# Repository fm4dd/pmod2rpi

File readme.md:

## PMOD2RPI

### Description

PMOD2RPI is a PMOD-compatible Interface Board for the Raspberry Pi B-type GPIO connector. It provides a total of four PMOD connectors to run PMOD-compatible modules on the Raspberry Pi.  This board is compatible to PMOD interface standard v1.3.1 by Digilent Inc. The PMOD (peripheral module interface) standard enables simple plug-in connectivity between FPGA or microcontroller development boards, and a range of input/output modules.

This design is registered under the OSHWA Open Source Hardware Self-Certification:  

 While all connectors provide digital IO, they also double as serial bus connectors for I2C and SPI modules. To aid troubleshooting, a set of Keystone miniature testpins can be fitted to create access for oscilloscope and DMM monitoring. A Seeeduino XIAO footprint has been added to additionally drive two of the four PMOD's, or to communicate with the RPi. The XIAO is optional, and can operate with the board "standalone" if needed.

#### I2C /SPI signal switching on PMOD1

The PMOD interface standard v1.3.1 added a new extended I2C connector type 6A, which runs the I2C bus signals over the same pins 3/4 that are already used for SPI. In order to allow both bus types to be used on a single connector, switch SW3 allows to swap the I2C signals between pins 3/4 and 9/10 on PMOD1.

See also http://fpga.fm4dd.com/

### Schematic

### Hardware Versions

| Version | Gerber | Schema |
|---------|--------|--------|
| 1.0     |[20210821-pmod2rpi-gerber-v10.zip](release/v10/20210821-pmod2rpi-gerber-v10.zip) | [20210821-pmod2rpi-schema-v10.pdf](release/v10/20210821-pmod2rpi-schema-v10.pdf) |

### Pin Assignments

Pin assigments are listed in the separate [pmod2rpi-pinout.md](pmod2rpi-pinout.md) file.
Below are simplified schematics for the XIAO MCU-specific connectivity.

#### XIAO - PMOD1:

A multi-purpose double-row connector that can used as GPIO Type-1 and Type-1A, SPI Type-2 and Type-2A, or I2C Type-6 or Type-6A, depending on the pin configuration of the XIAO.

#### XIAO - PMOD2:

A double-row connector that can use only the upper row for GPIO Type-1, SPI Type-2, or I2C Type-6 configurations. The lower pins are connected to the Raspberry Pi only.

#### XIAO - Raspberry Pi:

A set of XIAO pins are shared with the Raspberry Pi that can be used to establish GPIO and SPI connections. With bitbanging, I2C is also possible for data exchange between the Pi and the XIAO.

### Example Code

| Platform | Folder | Description |
|----------|--------|-------------|
|Raspberry Pi |[pi-gpiotest](examples/pi-gpiotest)   | simple GPIO test program for digital IO PMODs, such as Digilent's PMOD8LD |
|Raspberry Pi |[pi-tca6424a](https://github.com/fm4dd/pmod-i2c24io/tree/master/examples/pi-tca6424a)   | I2C module driver 'C' program to control the I2C expander module PMOD-I2C24IO connected to PMOD4 |
|Arduino      |[xiao-digital-io](examples/xiao-digital-io)   | Tests digital IO using the Digilent 8-Led PMOD 8LD connected to PMOD1 |
|Arduino      |[xiao-pmod1-24iodemo](https://github.com/fm4dd/pmod-i2c24io/tree/master/examples/xiao-pmod1-24iodemo)   | Creates a lightshow demo by rotating binary patterns over the 24 IO pins, lighting up connected LEDs |

I2C24IO PMOD demos are stored within the PMOD's repo located at [https://github.com/fm4dd/pmod-i2c24io](https://github.com/fm4dd/pmod-i2c24io).

### Board Pictures
I2C24IO PMOD connected to the RPi PMOD Interface board connector PMOD1, running the "xiao-pmod1-i2c24io" example program on the Seeeduino XIAO (Cortex M0) in "standalone" mode:

Raspberry Pi I2C signal measurements on the PMOD2RPI board:

Raspberry Pi operating the I2C24IO-PMOD module connected to PMOD4 on the PMOD2RPI board:

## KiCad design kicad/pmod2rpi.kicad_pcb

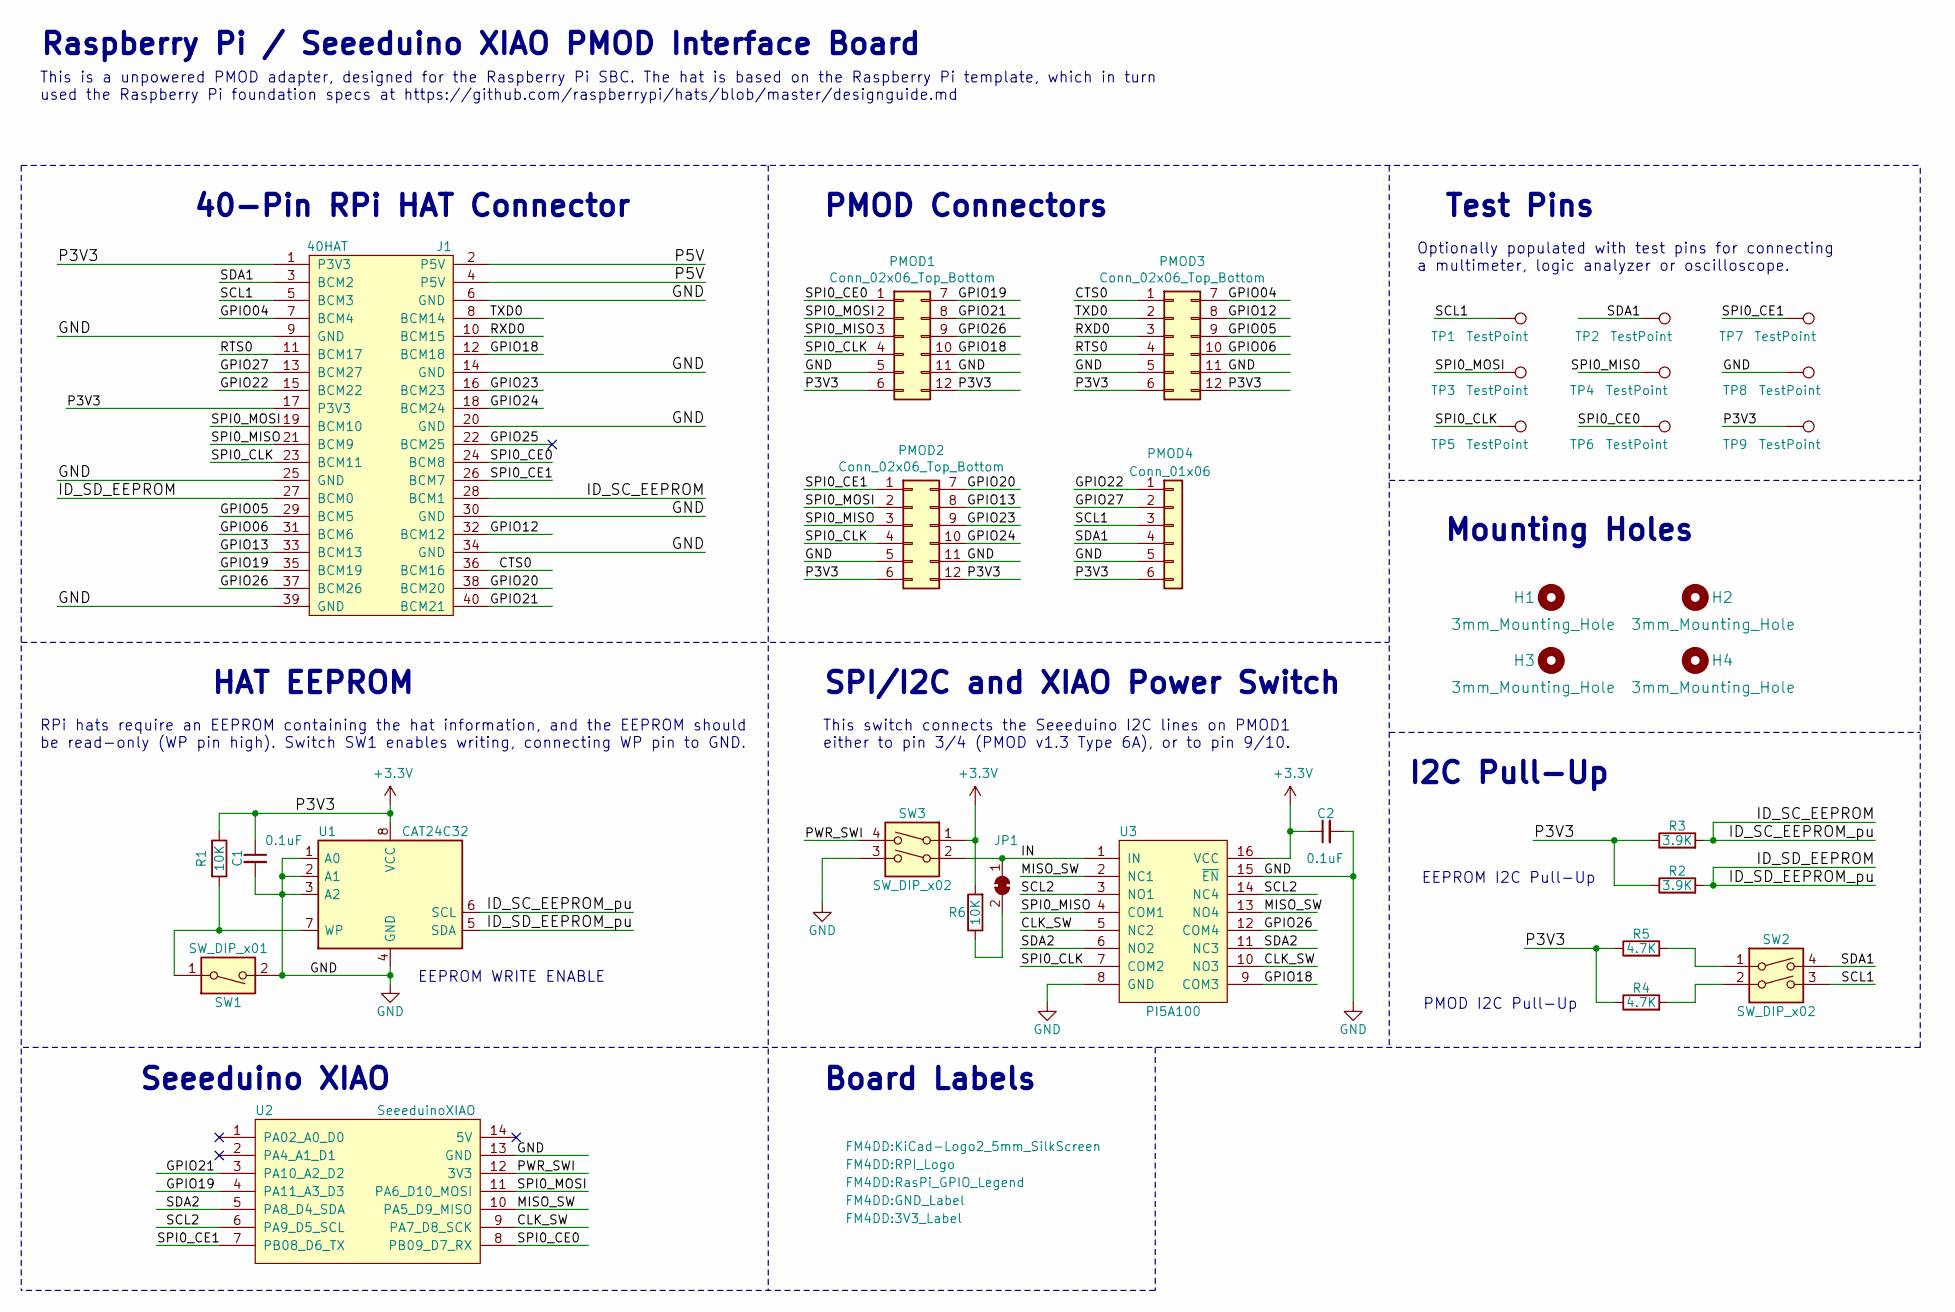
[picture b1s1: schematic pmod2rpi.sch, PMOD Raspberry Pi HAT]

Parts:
C1, C2: 0.1uF; C_0402_1005Metric
H1, H2, H3, H4: 3mm_Mounting_Hole; NPTH_3mm_ID
J1: 40HAT; PinSocket_2x20_P2.54mm_Vertical
JP1: SolderJumper_2_Bridged; SolderJumper-2_P1.3mm_Bridged_Pad1.0x1.5mm
L1: Logo_KiCad_5mm; KiCad-Logo2_5mm_SilkScreen
L2: Logo_RPI; RPI_Logo
L3: Pinout_RPI_GPIO; RasPi_GPIO_Legend
L4: GND_Label
L5: 3V3_Label
PMOD1, PMOD2, PMOD3: Conn_02x06_Top_Bottom; PMODPinSocket_2x06_P2.54mm_Horizontal
PMOD4: Conn_01x06; PMODPinSocket_1x06_P2.54mm_Horizontal
R1, R6: 10K; R_0603_1608Metric
R2, R3: 3.9K; R_0603_1608Metric
R4, R5: 4.7K; R_0603_1608Metric
SW1: SW_DIP_x01; SW_DIP_SPSTx01_XKB_DSIC01LS
SW2, SW3: SW_DIP_x02; SW_DIP_SPSTx02_XKB_DSIC02LS
TP1, TP2, TP3, TP4, TP5, TP6, TP7, TP8, TP9: TestPoint; TestPoint_Keystone_5000-5004_Miniature
U1: CAT24C32; SOIC-8_3.9x4.9mm_P1.27mm
U2: SeeeduinoXIAO; SeeeduinoXIAO-14P-2.54-21X17.8MM
U3: PI5A100; QSOP-16_3.9x4.9mm_P0.635mm

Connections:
+3V3: C1.1, C2.1, J1.1 (P3V3), J1.17 (P3V3), PMOD1.6, PMOD1.12, PMOD2.6, PMOD2.12, PMOD3.6, PMOD3.12, PMOD4.6, R1.1, R2.1, R3.1, R4.1, R5.1, R6.2, SW3.1, TP9.1, U1.8 (VCC), U3.16 (VCC)
/CLK_SW: U2.9 (PA7_D8_SCK), U3.5 (NC2), U3.10 (NO3)
/CTS0: J1.36 (BCM16), PMOD3.1
/GPIO04: J1.7 (BCM4), PMOD3.7
/GPIO05: J1.29 (BCM5), PMOD3.9
/GPIO06: J1.31 (BCM6), PMOD3.10
/GPIO12: J1.32 (BCM12), PMOD3.8
/GPIO13: J1.33 (BCM13), PMOD2.8
/GPIO18: J1.12 (BCM18), PMOD1.10, U3.9 (COM3)
/GPIO19: J1.35 (BCM19), PMOD1.7, U2.4 (PA11_A3_D3)
/GPIO20: J1.38 (BCM20), PMOD2.7
/GPIO21: J1.40 (BCM21), PMOD1.8, U2.3 (PA10_A2_D2)
/GPIO22: J1.15 (BCM22), PMOD4.1
/GPIO23: J1.16 (BCM23), PMOD2.9
/GPIO24: J1.18 (BCM24), PMOD2.10
/GPIO26: J1.37 (BCM26), PMOD1.9, U3.12 (COM4)
/GPIO27: J1.13 (BCM27), PMOD4.2
/ID_SC_EEPROM: J1.28 (BCM1), R3.2, U1.6 (SCL)
/ID_SD_EEPROM: J1.27 (BCM0), R2.2, U1.5 (SDA)
/IN: JP1.1 (A), SW3.2, U3.1 (IN)
/MISO_SW: U2.10 (PA5_D9_MISO), U3.2 (NC1), U3.13 (NO4)
/P5V: J1.2 (P5V), J1.4 (P5V)
/PWR_SWI: SW3.4, U2.12 (3V3)
/RTS0: J1.11 (BCM17), PMOD3.4
/RXD0: J1.10 (BCM15), PMOD3.3
/SCL1: J1.5 (BCM3), PMOD4.3, SW2.3, TP1.1
/SCL2: U2.6 (PA9_D5_SCL), U3.3 (NO1), U3.14 (NC4)
/SDA1: J1.3 (BCM2), PMOD4.4, SW2.4, TP2.1
/SDA2: U2.5 (PA8_D4_SDA), U3.6 (NO2), U3.11 (NC3)
/SPI0_CE0: J1.24 (BCM8), PMOD1.1, TP6.1, U2.8 (PB09_D7_RX)
/SPI0_CE1: J1.26 (BCM7), PMOD2.1, TP7.1, U2.7 (PB08_D6_TX)
/SPI0_CLK: J1.23 (BCM11), PMOD1.4, PMOD2.4, TP5.1, U3.7 (COM2)
/SPI0_MISO: J1.21 (BCM9), PMOD1.3, PMOD2.3, TP4.1, U3.4 (COM1)
/SPI0_MOSI: J1.19 (BCM10), PMOD1.2, PMOD2.2, TP3.1, U2.11 (PA6_D10_MOSI)
/TXD0: J1.8 (BCM14), PMOD3.2
GND: C1.2, C2.2, J1.6 (GND), J1.9 (GND), J1.14 (GND), J1.20 (GND), J1.25 (GND), J1.30 (GND), J1.34 (GND), J1.39 (GND), PMOD1.5, PMOD1.11, PMOD2.5, PMOD2.11, PMOD3.5, PMOD3.11, PMOD4.5, SW1.2, SW3.3, TP8.1, U1.1 (A0), U1.2 (A1), U1.3 (A2), U1.4 (GND), U2.13 (GND), U3.8 (GND), U3.15 (~EN)
unnamed: JP1.2 (B), R6.1
unnamed: R1.2, SW1.1, U1.7 (WP)
unnamed: R4.2, SW2.2
unnamed: R5.2, SW2.1

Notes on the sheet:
EEPROM WRITE ENABLE
I2C Pull-Up
HAT EEPROM
Mounting Holes
40-Pin RPi HAT Connector
RPi hats require an EEPROM containing the hat information, and the EEPROM should be read-only (WP pin high). Switch SW1 enables writing, connecting WP pin to GND.
This is a unpowered PMOD adapter, designed for the Raspberry Pi SBC. The hat is based on the Raspberry Pi template, which in turn used the Raspberry Pi foundation specs at https://github.com/raspberrypi/hats/blob/master/designguide.md
PMOD Connectors
EEPROM I2C Pull-Up
Optionally populated with test pins for connecting a multimeter, logic analyzer or oscilloscope.
Test Pins
Board Labels
Raspberry Pi / Seeeduino XIAO PMOD Interface Board
SPI/I2C and XIAO Power Switch
This switch connects the Seeeduino I2C lines on PMOD1 either to pin 3/4 (PMOD v1.3 Type 6A), or to pin 9/10.
Seeeduino XIAO
PMOD I2C Pull-Up

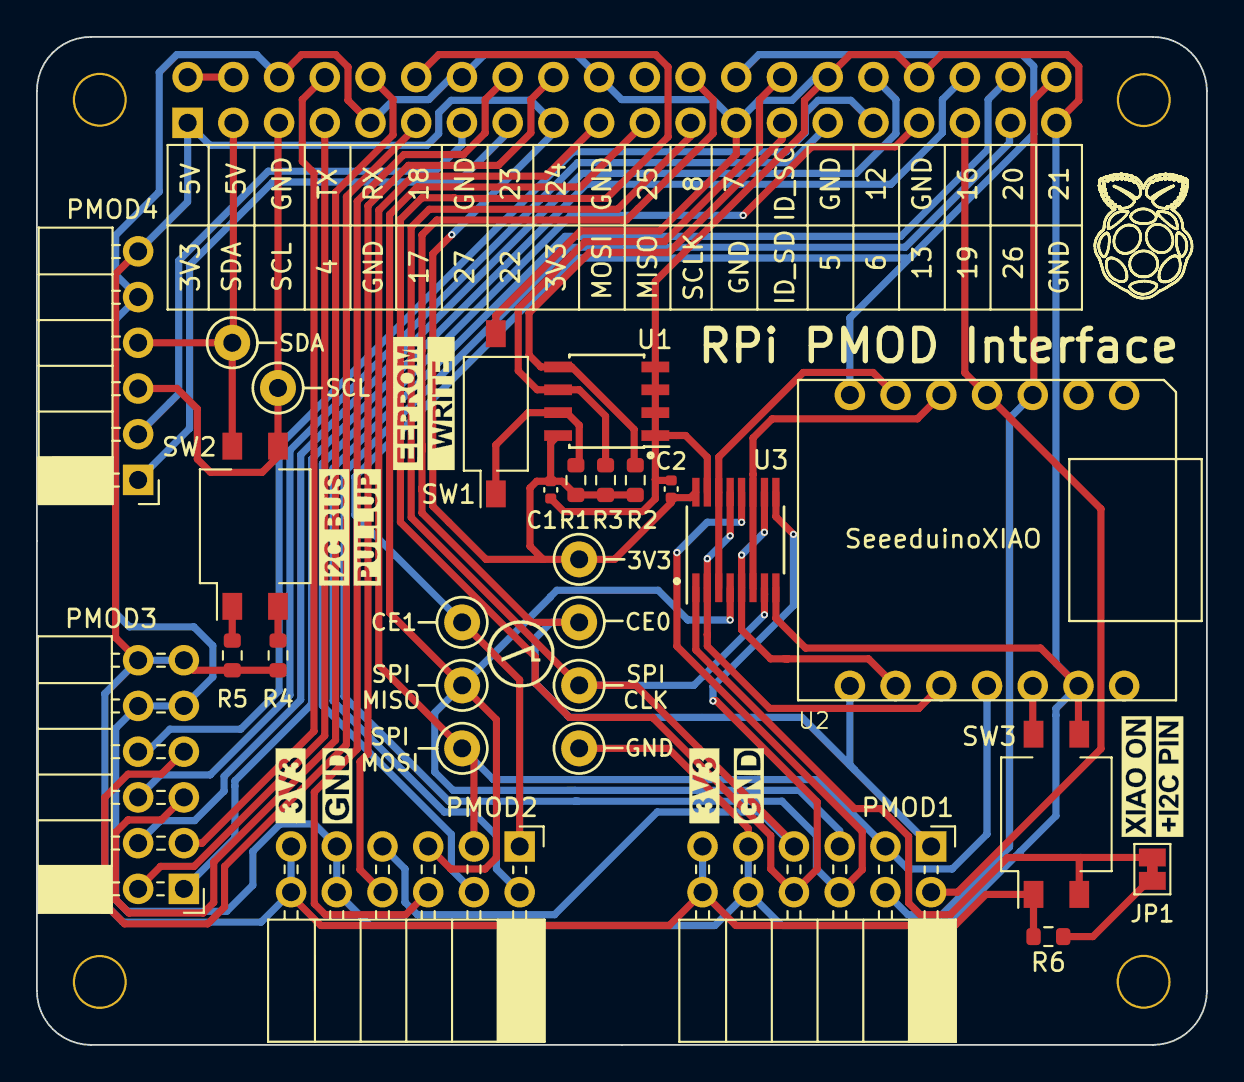
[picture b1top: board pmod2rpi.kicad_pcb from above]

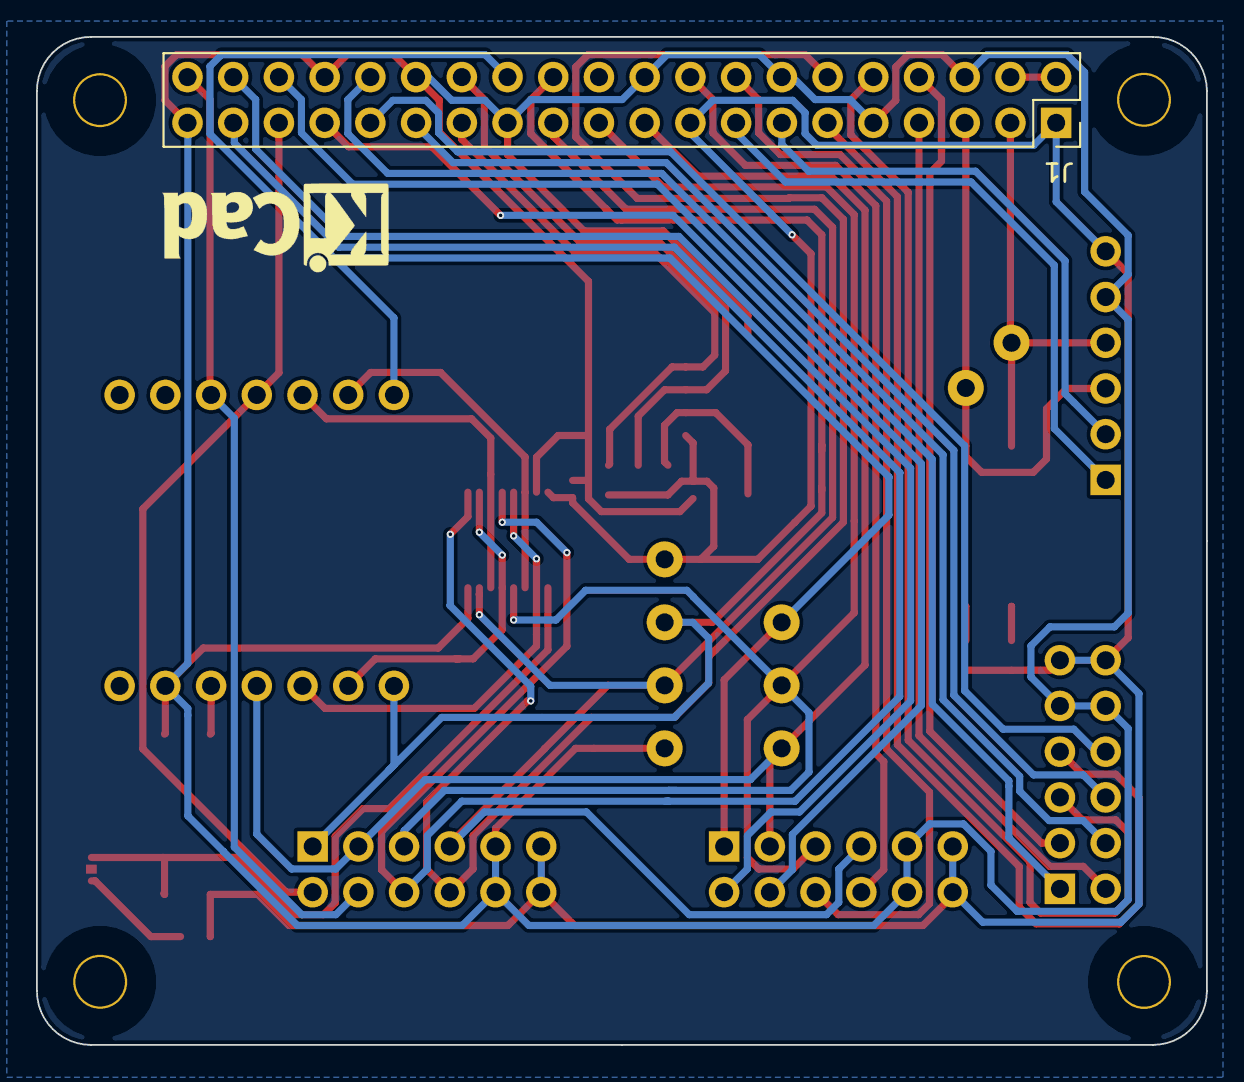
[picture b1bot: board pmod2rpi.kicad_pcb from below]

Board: 2 copper layers, 65.0 x 56.0 mm, 41 parts (2 on the bottom side), 40 nets.

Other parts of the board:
L4#2: GND_Label
L5#2: 3V3_Label
SN1: JLCPCB_serial_location; JLCPCB_Order_Number_Placeholder

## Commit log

2021-09-26 initial check in
2021-10-02 update readme and license
2021-10-02 add GPIO example
2021-10-09 update pinout
2021-10-10 add pmod-7seg9 example

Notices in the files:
kicad/pmod2rpi.sch:
License: CC-BY-SA 4.0
